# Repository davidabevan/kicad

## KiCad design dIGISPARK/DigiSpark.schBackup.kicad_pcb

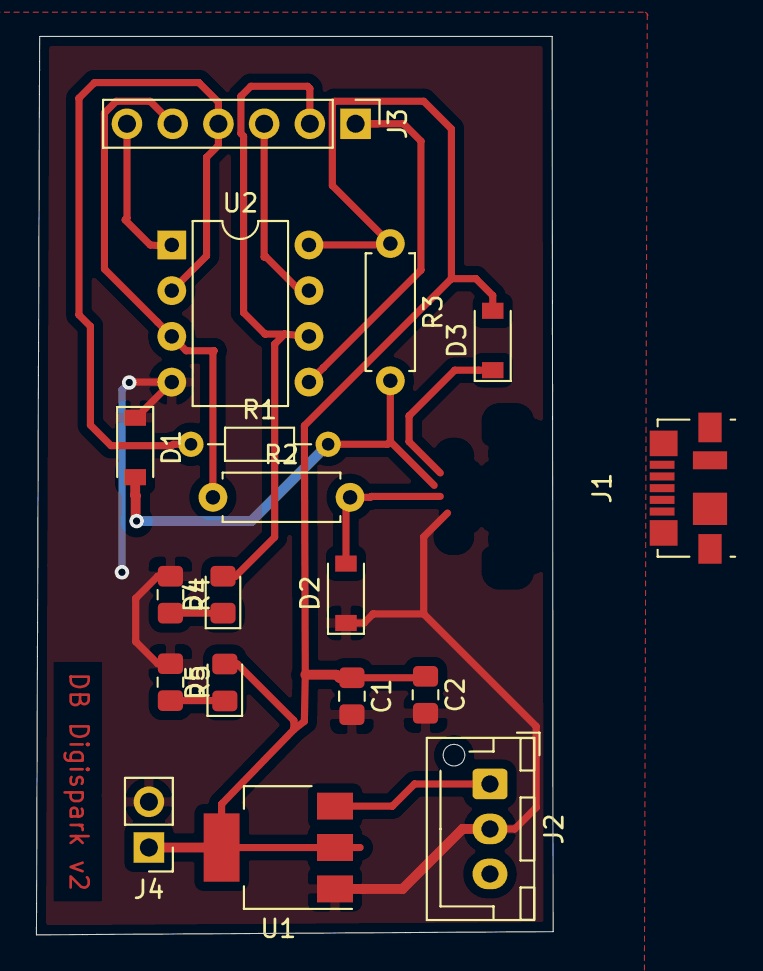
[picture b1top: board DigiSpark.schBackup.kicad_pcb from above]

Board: 2 copper layers, 28.7 x 49.9 mm, 18 parts (0 on the bottom side), 14 nets.

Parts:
C1: 4.7uf; C_0805_2012Metric_Pad1.15x1.40mm_HandSolder
C2: 0.1uf; C_0805_2012Metric_Pad1.15x1.40mm_HandSolder
D1, D2: D_Zener3.6v; D_SOD-123
D3: MBR0520LT; D_SOD-123
D4: LED; LED_0805_2012Metric_Pad1.15x1.40mm_HandSolder
D5: PWR; LED_0805_2012Metric_Pad1.15x1.40mm_HandSolder
J1: USB_B; USB_Micro-B_Molex_47346-0001
J2: Conn_01x02_Male; JST_XH_B3B-XH-AM_1x03_P2.50mm_Vertical
J3: Conn_01x06_Female; PinHeader_1x06_P2.54mm_Vertical
J4: Conn_01x02_Male; PinHeader_1x02_P2.54mm_Vertical
R1: 68r; R_Axial_DIN0204_L3.6mm_D1.6mm_P7.62mm_Horizontal
R2: 68r; R_Axial_DIN0207_L6.3mm_D2.5mm_P7.62mm_Horizontal
R3: 1k3; R_Axial_DIN0207_L6.3mm_D2.5mm_P7.62mm_Horizontal
R4, R5: 120r; R_0805_2012Metric_Pad1.15x1.40mm_HandSolder
U1: AMS1117-5.0; SOT-223-3_TabPin2
U2: ATtiny85-20PU; DIP-8_W7.62mm

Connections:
+5V: C1.1, C2.1, D3.2, D5.2, J4.1, R3.1, U1.2, U2.8
+BATT: J2.1, U1.3
/5v: D3.1, J1.1
/PB1: D4.2, J3.2, U2.6
/PB2: J3.3, U2.7
/PB4: J3.5, R2.1, U2.3
/PB5: J3.6, U2.1
/Pb0: J3.1, U2.5
/Pb3: J3.4, R1.1, U2.2
/d+: D2.2, J1.3, R2.2
/d-: D1.2, J1.2, R1.2, R3.2
GND: C1.2, C2.2, D1.1, D2.1, J1.4, J1.5, J2.2, J4.2, R4.1, R5.1, U1.1, U2.4
unnamed: D4.1, R4.2
unnamed: D5.1, R5.2

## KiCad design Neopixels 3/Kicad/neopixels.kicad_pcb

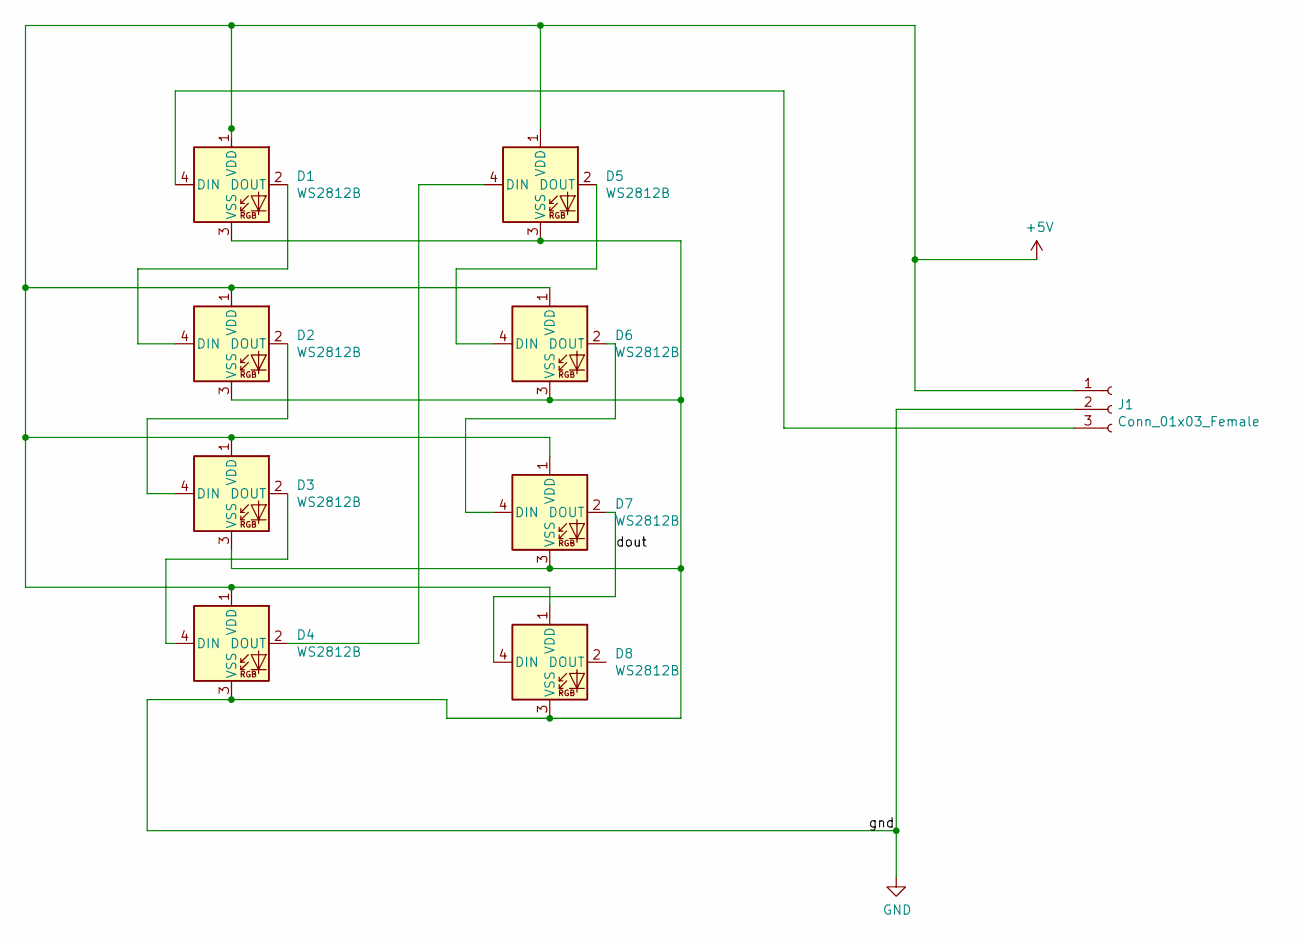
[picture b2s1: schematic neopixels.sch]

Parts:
D1, D2, D3, D4, D5, D6, D7, D8: WS2812B; LED_WS2812B_PLCC4_5.0x5.0mm_P3.2mm
J1: Conn_01x03_Female; JST_SH_BM03B-SRSS-TB_1x03-1MP_P1.00mm_Vertical

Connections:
+5V: D1.1 (VDD), D2.1 (VDD), D3.1 (VDD), D4.1 (VDD), D5.1 (VDD), D6.1 (VDD), D7.1 (VDD), D8.1 (VDD), J1.1
GND: D1.3 (VSS), D2.3 (VSS), D3.3 (VSS), D4.3 (VSS), D5.3 (VSS), D6.3 (VSS), D7.3 (VSS), D8.3 (VSS), J1.2
unnamed: D1.2 (DOUT), D2.4 (DIN)
unnamed: D1.4 (DIN), J1.3
unnamed: D2.2 (DOUT), D3.4 (DIN)
unnamed: D3.2 (DOUT), D4.4 (DIN)
unnamed: D4.2 (DOUT), D5.4 (DIN)
unnamed: D5.2 (DOUT), D6.4 (DIN)
unnamed: D6.2 (DOUT), D7.4 (DIN)
unnamed: D7.2 (DOUT), D8.4 (DIN)

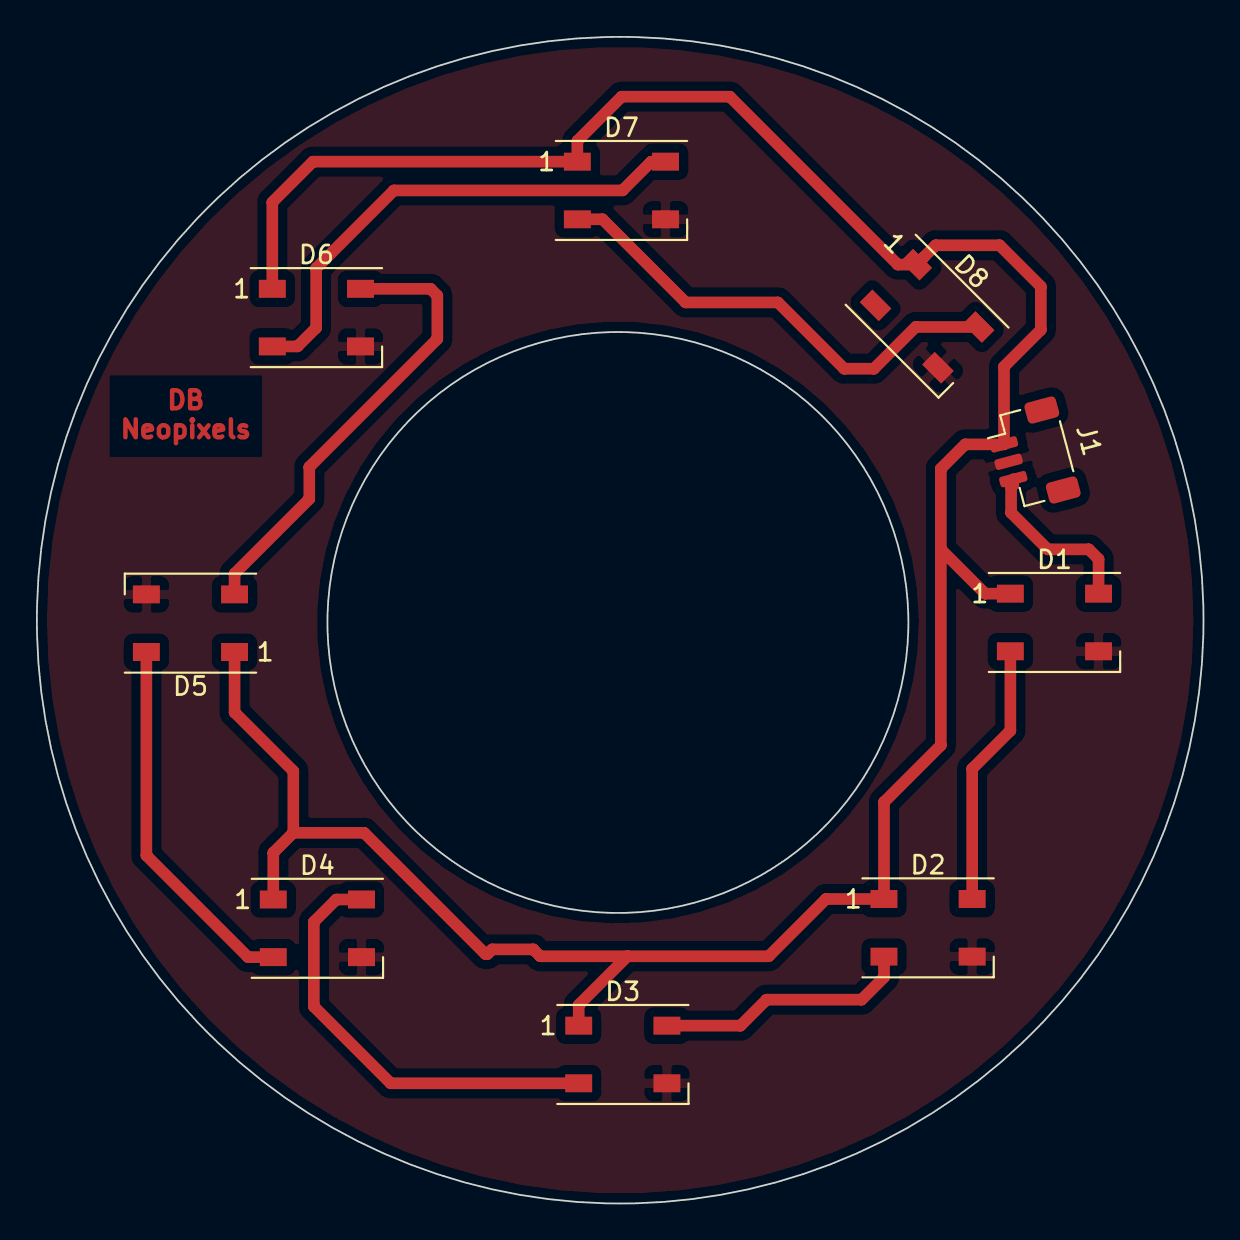
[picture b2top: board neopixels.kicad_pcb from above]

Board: 2 copper layers, 64.8 x 64.8 mm, 9 parts (0 on the bottom side), 10 nets.

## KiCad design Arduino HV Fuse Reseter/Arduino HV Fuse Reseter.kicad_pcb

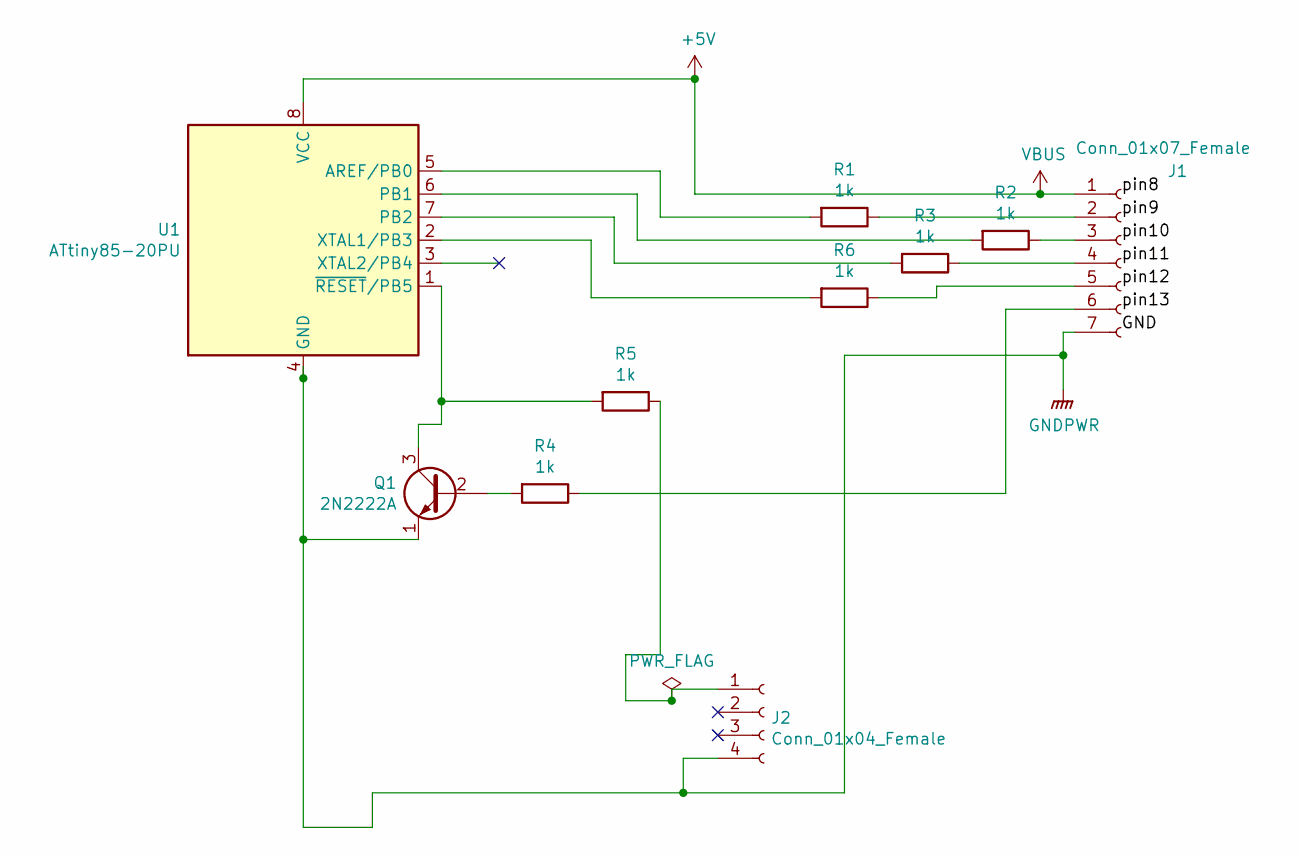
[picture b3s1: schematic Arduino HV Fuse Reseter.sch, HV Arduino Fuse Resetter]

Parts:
J1: Conn_01x07_Female; PinHeader_1x07_P2.54mm_Vertical
J2: Conn_01x04_Female; JST_XH_B4B-XH-A_1x04_P2.50mm_Vertical
Q1: 2N2222A; TO-39-3
R1, R2, R3, R4, R5, R6: 1k; R_Axial_DIN0204_L3.6mm_D1.6mm_P7.62mm_Horizontal
U1: ATtiny85-20PU; DIP-8_W7.62mm

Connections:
+5V: J1.1, U1.8 (VCC)
GNDPWR: J1.7, J2.4, Q1.1 (E), U1.4 (GND)
unnamed: J1.2, R1.1
unnamed: J1.3, R2.1
unnamed: J1.4, R3.1
unnamed: J1.5, R6.1
unnamed: J1.6, R4.1
unnamed: J2.1, R5.1
unnamed: Q1.2 (B), R4.2
unnamed: Q1.3 (C), R5.2, U1.1 (~RESET~/PB5)
unnamed: R1.2, U1.5 (AREF/PB0)
unnamed: R2.2, U1.6 (PB1)
unnamed: R3.2, U1.7 (PB2)
unnamed: R6.2, U1.2 (XTAL1/PB3)

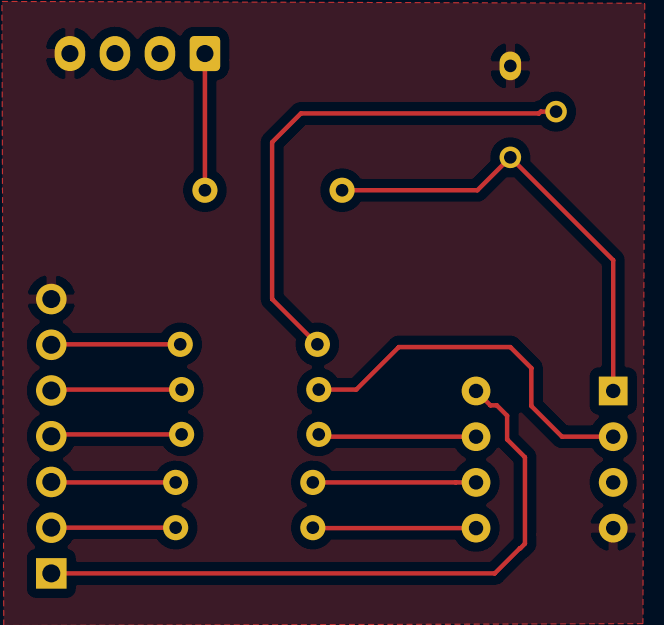
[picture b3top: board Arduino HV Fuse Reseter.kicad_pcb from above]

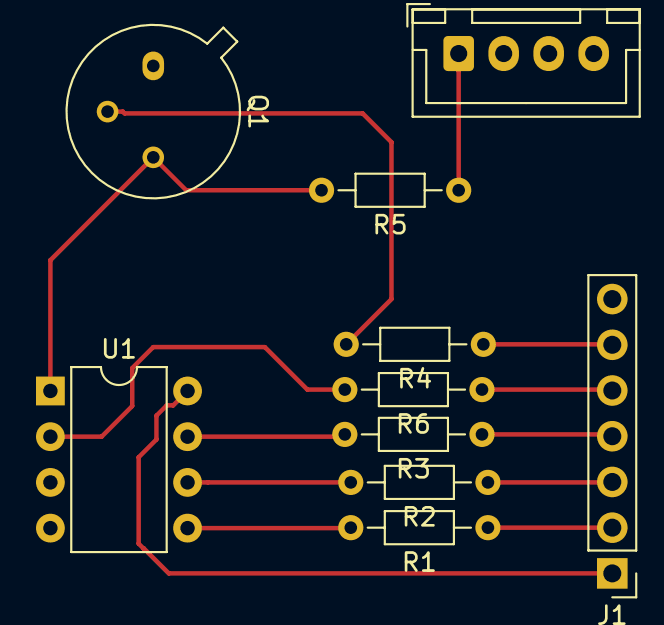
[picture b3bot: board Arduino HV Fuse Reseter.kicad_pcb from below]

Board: 2 copper layers, 10 parts (10 on the bottom side), 14 nets.

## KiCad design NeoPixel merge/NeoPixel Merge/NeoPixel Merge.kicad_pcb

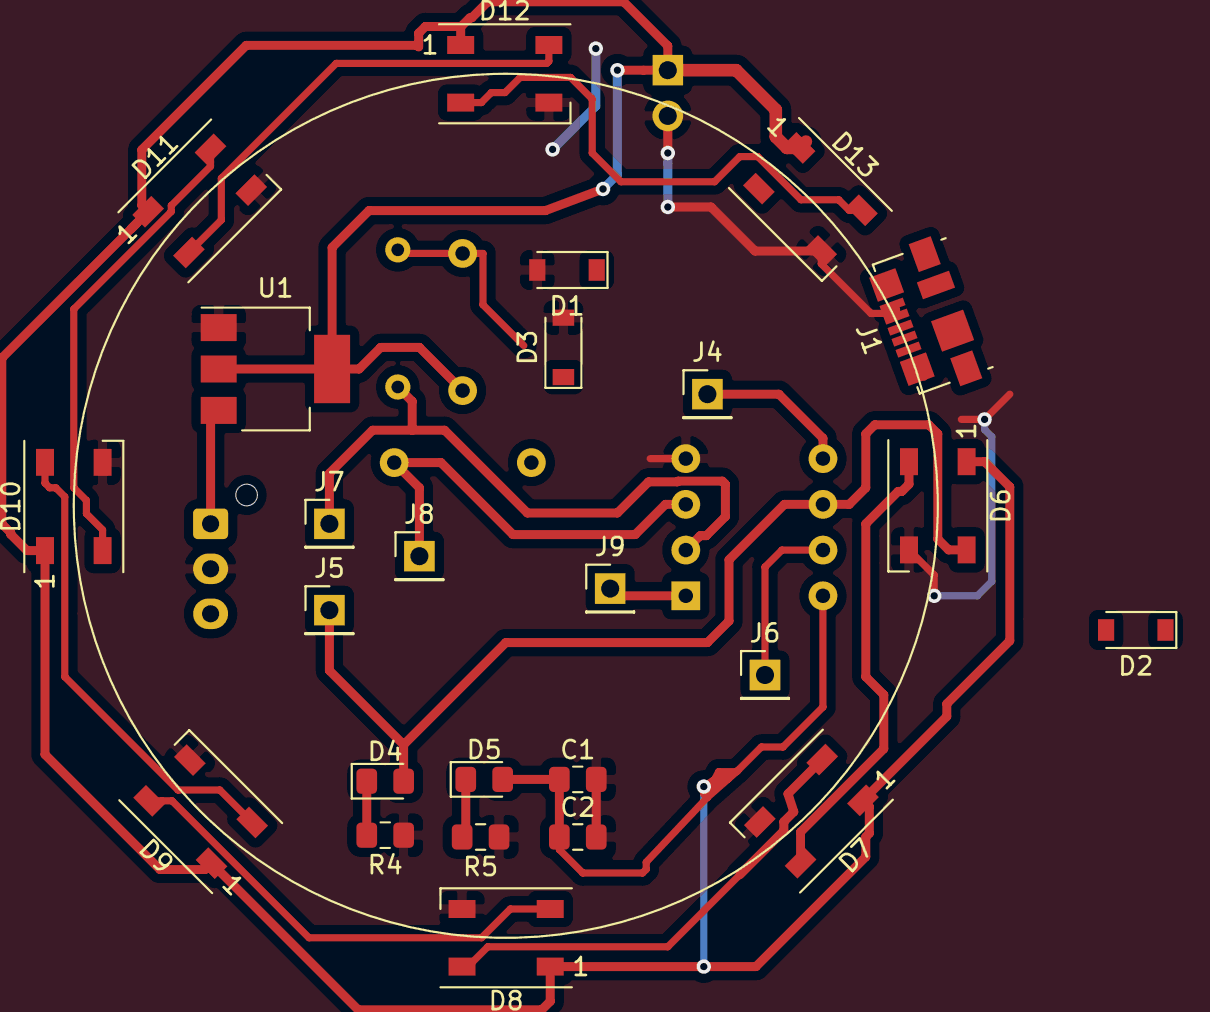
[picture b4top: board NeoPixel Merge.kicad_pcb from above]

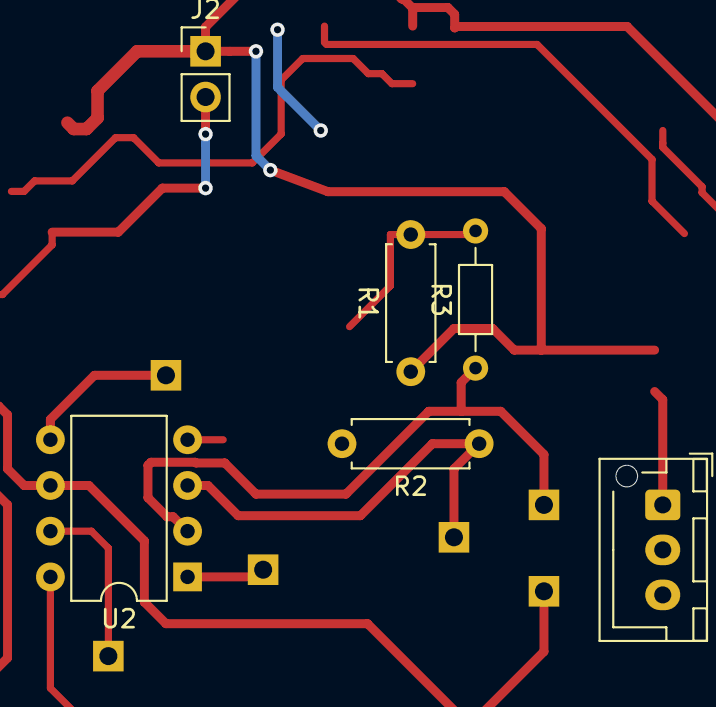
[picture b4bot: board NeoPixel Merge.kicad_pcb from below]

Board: 2 copper layers, 31 parts (6 on the bottom side), 21 nets.

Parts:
C1: 4.7uf; C_0805_2012Metric_Pad1.15x1.40mm_HandSolder
C2: 0.1uf; C_0805_2012Metric_Pad1.15x1.40mm_HandSolder
D1, D3: D_Zener3.6v; D_SOD-123
D2: MBR0520LT; D_SOD-123
D4: LED; LED_0805_2012Metric_Pad1.15x1.40mm_HandSolder
D5: PWR; LED_0805_2012Metric_Pad1.15x1.40mm_HandSolder
D6, D7, D8, D9, D10, D11, D12, D13: WS2812B; LED_WS2812B_PLCC4_5.0x5.0mm_P3.2mm
J1: USB_B; USB_Micro-B_Molex_47346-0001
J2: 5V; PinHeader_1x02_P2.54mm_Vertical
J3: Batt7.4V; JST_XH_B3B-XH-AM_1x03_P2.50mm_Vertical
J4, J5, J6, J7, J8, J9: Conn_01x01_Female; PinHeader_1x01_P2.54mm_Vertical
R1: 1k3; R_Axial_DIN0207_L6.3mm_D2.5mm_P7.62mm_Horizontal
R2: 68r; R_Axial_DIN0207_L6.3mm_D2.5mm_P7.62mm_Horizontal
R3: 68r; R_Axial_DIN0204_L3.6mm_D1.6mm_P7.62mm_Horizontal
R4, R5: 120r; R_0805_2012Metric_Pad1.15x1.40mm_HandSolder
U1: AMS1117-5.0; SOT-223-3_TabPin2
U2: ATtiny85-20PU; DIP-8_W7.62mm

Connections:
+5V: C1.1, C2.1, D2.2, D5.2, D6.1, D7.1, D8.1, D9.1, D10.1, D11.1, D12.1, D13.1, J2.1, R1.1, U1.2, U2.8
+BATT: J3.1, U1.3
/PB2: J6.1, U2.7
/PB4: J8.1, R2.1, U2.3
/PB5: J9.1, U2.1
/Pb0: J4.1, U2.5
/Pb3: J7.1, R3.1, U2.2
/Pixel Ring/dout: D12.2, D13.4
GND: C1.2, C2.2, D1.2, D3.2, D6.3, D7.3, D8.3, D9.3, D10.3, D11.3, D12.3, D13.3, J1.4, J1.5, J2.2, J3.2, R4.1, R5.1, U1.1, U2.4
unnamed: D1.1, J1.3, R2.2
unnamed: D2.1, J1.1
unnamed: D3.1, J1.2, R1.2, R3.2
unnamed: D4.1, R4.2
unnamed: D5.1, R5.2
unnamed: D6.2, D7.4
unnamed: D7.2, D8.4
unnamed: D8.2, D9.4
unnamed: D10.2, D11.4
unnamed: D9.2, D10.4
unnamed: D11.2, D12.4
PB1: D4.2, D6.4, J5.1, U2.6
